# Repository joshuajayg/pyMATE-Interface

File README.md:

# pyMATE-Interface
The physical connection between an Outback Power system and Raspberry Pi Zero

To be used with Jared's repo: http://github.com/jorticus/pymate

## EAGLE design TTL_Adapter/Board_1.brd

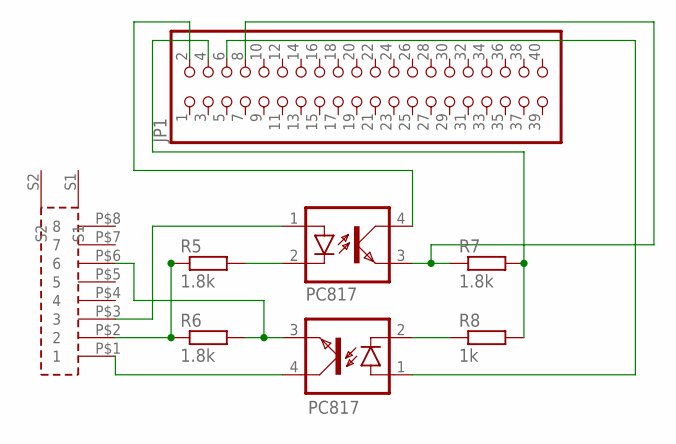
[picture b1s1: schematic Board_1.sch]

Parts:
JP1: PINHD-2X20-BIG; 2X20-BIG
OK1, OK2: PC817; DIL04
R5, R6, R7: 1.8k; 0207/10
R8: 1k; 0207/10
U$1: RJ-45

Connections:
unnamed: OK2.4 (COL), U$1.P$1 (1)
unnamed: R5.1, R6.1, U$1.P$2 (2)
unnamed: OK1.2 (C), R5.2
unnamed: OK2.3 (EMIT), R6.2, U$1.P$6 (6)
unnamed: OK1.1 (A), U$1.P$3 (3)
unnamed: JP1.6, OK2.1 (A)
unnamed: OK2.2 (C), R8.1
unnamed: JP1.8, OK1.3 (EMIT), R7.1
unnamed: JP1.4, R7.2, R8.2
unnamed: JP1.2, OK1.4 (COL)

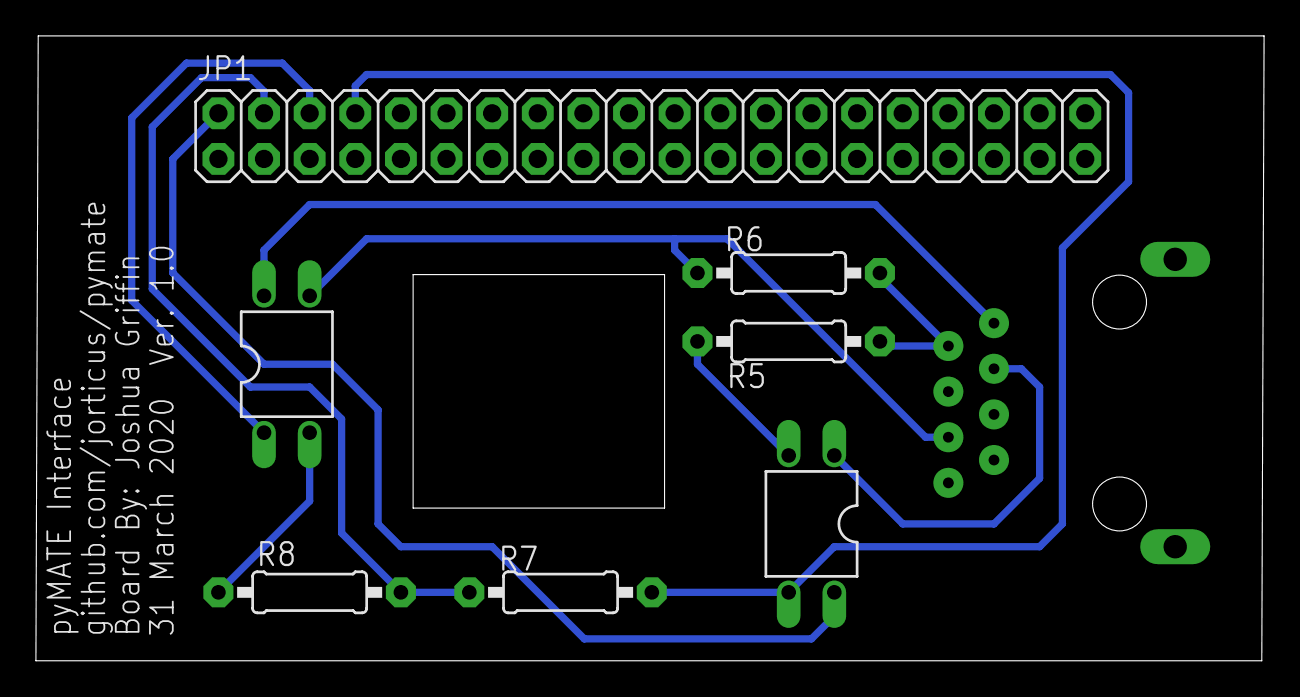
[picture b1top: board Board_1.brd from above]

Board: 2 copper layers, 68.4 x 34.8 mm, 8 parts (1 on the bottom side), 10 nets.

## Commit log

2020-04-01 Added files
